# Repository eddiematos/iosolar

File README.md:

# iosolar
Design files for a modular solar power system. These files are licensed with an open-source hardware license based on the Apache License Version 2.0, known as the Solderpad Hardware Licence Version 2.

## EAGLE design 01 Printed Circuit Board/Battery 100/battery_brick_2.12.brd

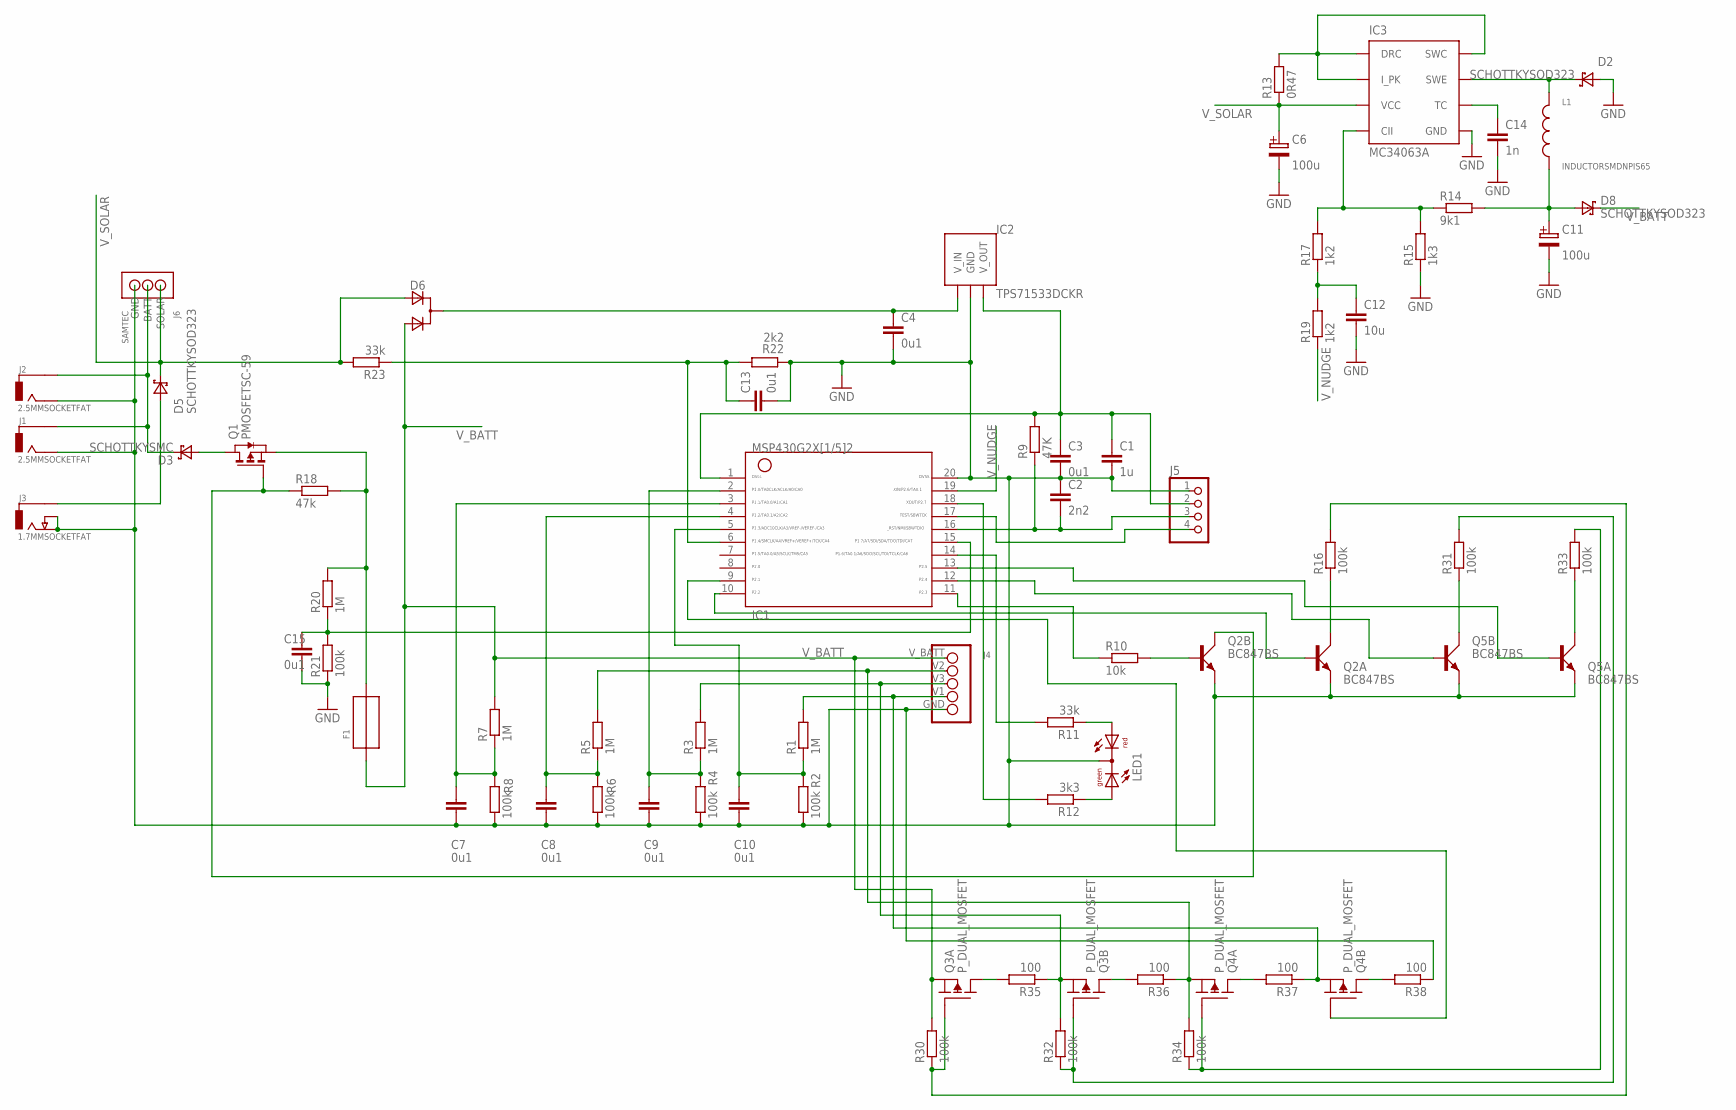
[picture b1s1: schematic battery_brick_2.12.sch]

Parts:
C1: 1u; C0603K
C2: 2n2; C0603K
C3: 0u1; C0603K
C4, C7, C8, C9, C10, C13, C15: 0u1; C0603
C6, C11: 100u; CAPCANVZH101
C12: 10u; C2012
C14: 1n; C0603
D2, D5, D8: SCHOTTKYSOD323; SOD323
D3: SCHOTTKYSMC; SMC
D6: D_2ASOT323; SOT323
F1: FUSE; 1812
IC1: G2X[1/5]2---PW20; PW20
IC2: TPS71533DCKR; SC70-5
IC3: MC34063A; SOIC8
J1, J2: 2.5MMSOCKETFAT; 2.5MMSOCKET-OBLONGFAT
J3: 1.7MMSOCKETFAT; 1.7MMSOCKET-OBLONGFAT
J4: S5B-PH-K-S
J5: PINHD-1X4; 1X04
J6: SAMTEC
L1: INDUCTORSMDNPIS65; INDUCTOR_NPIS65
LED1: DUOLED5MM
Q1: PMOSFETSC-59; SC-59
Q2, Q5: BC847BS; SOT363_PHILIPS
Q3, Q4: P_DUAL_MOSFET; SOT666
R1, R3, R5, R7: 1M; R0805
R2, R4, R6, R8: 100k; R0805
R9: 47K; R0603
R10: 10k; R0603
R11, R23: 33k; R0603
R12: 3k3; R0603
R13: 0R47; R1206
R14: 9k1; R0603
R15: 1k3; R0603
R16, R21, R30, R31, R32, R33, R34: 100k; R0603
R17, R19: 1k2; R0603
R18: 47k; R0603
R20: 1M; R0603
R22: 2k2; R0603
R35, R36, R37, R38: 100; M1206

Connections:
GND: C1.2, C2.1, C3.2, C4.2, C6.-VE, C7.2, C8.2, C9.2, C10.2, C11.-VE, C12.2, C13.2, C14.2, C15.2, D2.ANODE, IC1.20, IC2.GND, IC3.GND, J1.-VE, J2.-VE, J3.-VE, J3.P$3, J4.GND, J5.1, J6.GND, LED1.K (C), Q2.1 (E), Q2.4 (E), Q5.1 (E), Q5.4 (E), R2.1, R4.1, R6.1, R8.1, R15.1, R21.1, R22.1, R38.1
unnamed: IC1.17, J5.4
unnamed: C10.1, IC1.5, R1.1, R2.2
unnamed: F1.2, Q1.S, R18.2, R20.2
unnamed: C9.1, IC1.2, R3.1, R4.2
unnamed: D3.CATHODE, J1.+VE, J2.+VE, J6.BATT
unnamed: C8.1, IC1.4, R5.1, R6.2
unnamed: C7.1, IC1.3, R7.1, R8.2
unnamed: C15.1, IC1.15, R20.1, R21.2
unnamed: Q2.5 (B), R10.2
unnamed: IC1.14, R11.2
unnamed: J4.V1, Q4.4 (S), R1.2, R37.1
unnamed: D5.ANODE, J3.+VE
unnamed: LED1.AG, R12.1
unnamed: LED1.AR, R11.1
unnamed: J4.V3, Q3.4 (S), R3.2, R32.2, R35.1
unnamed: J4.V2, Q4.1 (S), R5.2, R34.2, R36.1
unnamed: IC3.DRC, IC3.I_PK, IC3.SWC, R13.2
unnamed: D3.ANODE, Q1.D
unnamed: Q1.G, Q2.3 (C), R18.1
unnamed: IC1.18, R12.2
unnamed: IC3.CII, R14.1, R15.2, R17.2
unnamed: D2.CATHODE, IC3.SWE, L1.P$1
unnamed: C13.1, IC1.6, R22.2, R23.1
unnamed: C12.1, R17.1, R19.2
unnamed: C11.+VE (P$1+), D8.ANODE, L1.P$2, R14.2
unnamed: C14.1, IC3.TC
unnamed: Q3.6 (D), R35.2
unnamed: Q5.3 (C), R31.1
unnamed: IC1.9, Q4.5 (G)
unnamed: C2.2, IC1.16, J5.3, R9.1
unnamed: Q3.2 (G), R16.2, R30.1
unnamed: Q3.5 (G), R31.2, R32.1
unnamed: Q4.2 (G), R33.2, R34.1
unnamed: Q5.6 (C), R33.1
unnamed: Q2.6 (C), R16.1
unnamed: Q4.3 (D), R38.2
unnamed: IC1.11, R10.1
unnamed: IC1.10, Q2.2 (B)
unnamed: IC1.12, Q5.5 (B)
unnamed: IC1.13, Q5.2 (B)
unnamed: Q3.3 (D), R36.2
unnamed: Q4.6 (D), R37.2
VCC: C1.1, C3.1, IC1.1, IC2.OUT (V_OUT), J5.2, R9.2
V_BATT: D6.3 (A2), D8.CATHODE, F1.1, J4.V_BATT, Q3.1 (S), R7.2, R30.2
V_NUDGE: IC1.19, R19.1
V_REGIN: C4.1, D6.1 (C), IC2.IN (V_IN)
V_SOLAR: C6.+VE (P$1+), D5.CATHODE, D6.2 (A1), IC3.VCC, J6.SOLAR, R13.1, R23.2

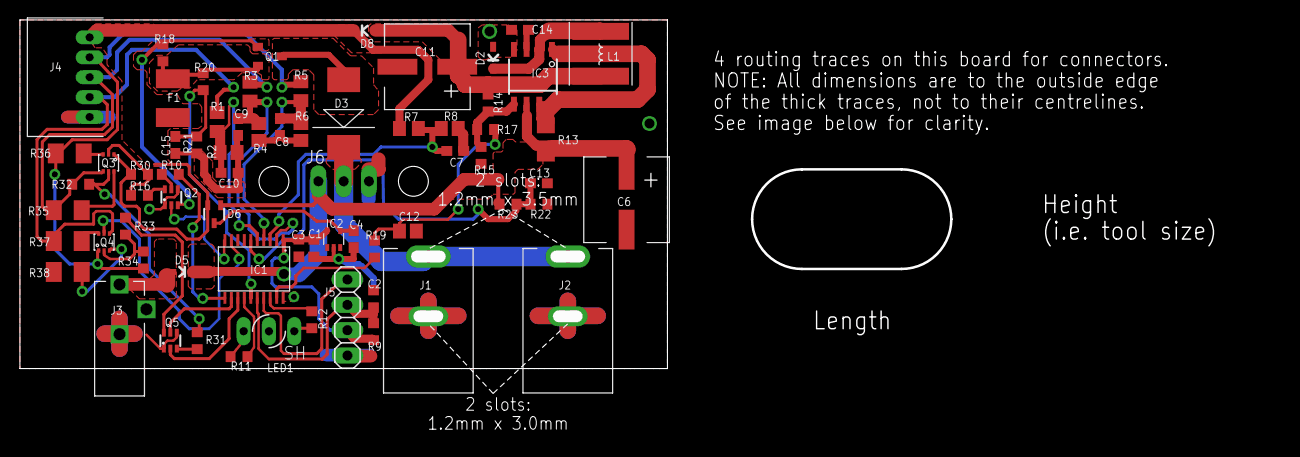
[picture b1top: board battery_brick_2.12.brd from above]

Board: 2 copper layers, 65.0 x 35.0 mm, 68 parts (0 on the bottom side), 48 nets.

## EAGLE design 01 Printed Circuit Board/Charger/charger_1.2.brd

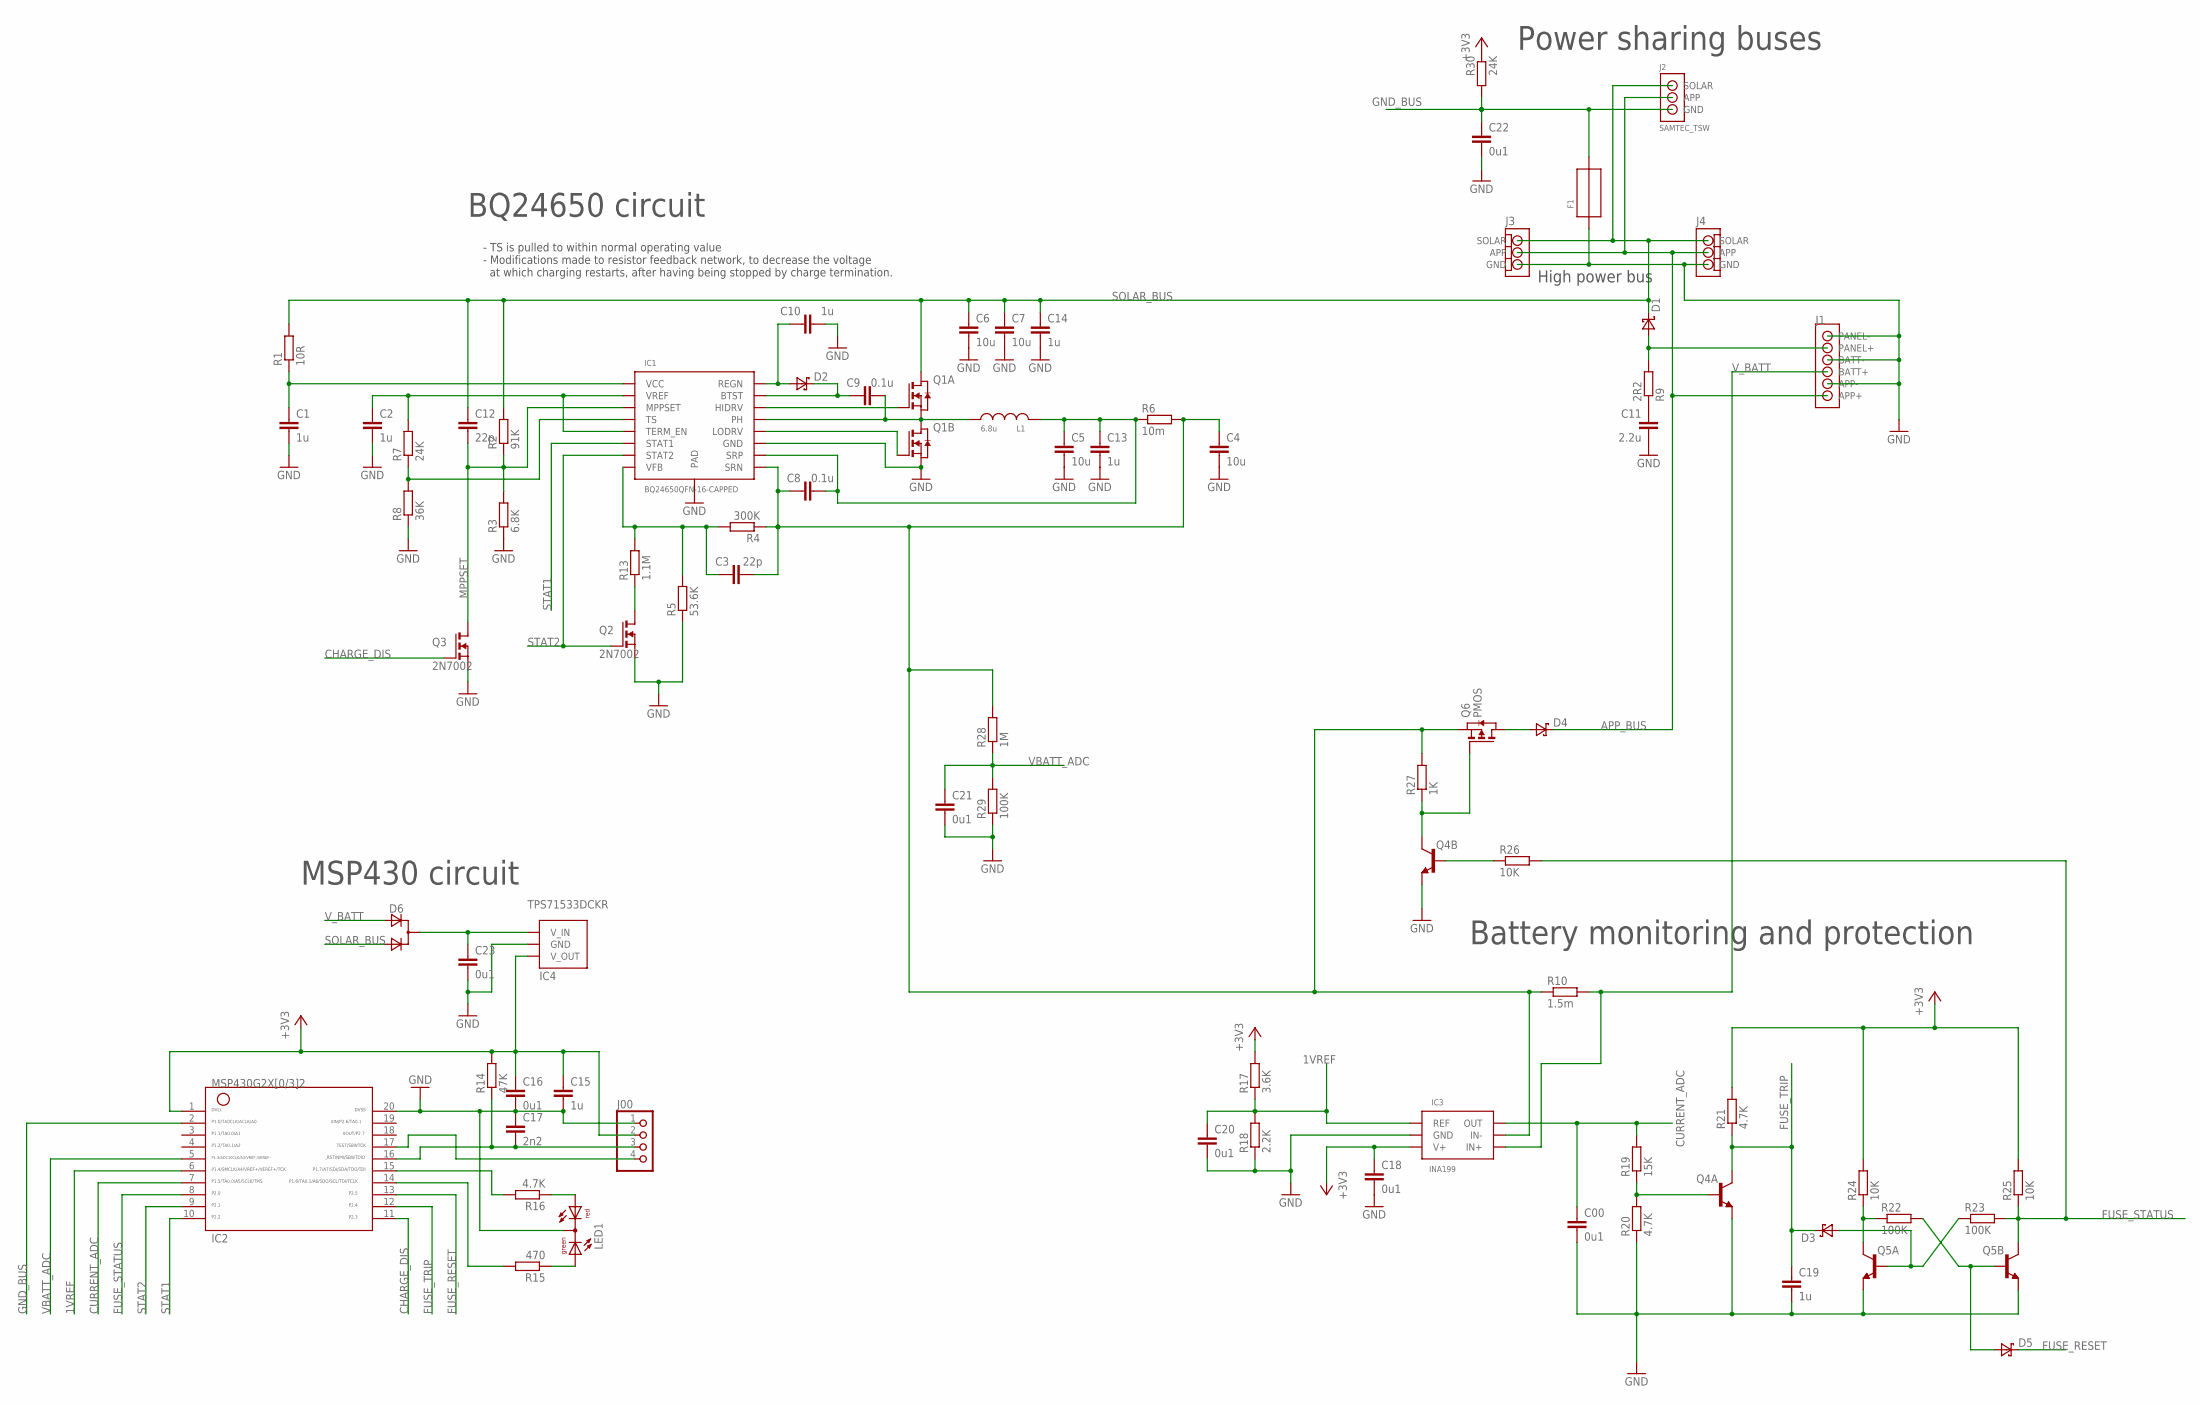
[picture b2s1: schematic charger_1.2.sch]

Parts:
C00, C16, C18, C20, C21, C22, C23: 0u1; C0603K
C1, C2, C10, C13, C14, C19: 1u; C0603
C3, C12: 22p; C0603
C4, C5, C6, C7: 10u; C1206
C8, C9: 0.1u; C0603
C11: 2.2u; C0603
C15: 1u; C0603K
C17: 2n2; C0603K
D1: SCHOTTKYDPAK; DPAK
D2: SCHOTTKYSOT23; SOT23
D3, D5: SCHOTTKYSOD-523F; SOD-523F
D4: SCHOTTKYSO8-FLAT; SO8-FLAT
D6: D_2ASOT23; SOT-23
F1: FUSE2920; 2920
IC1: BQ24650QFN-16-CAPPED; QFN-16-CAPPED
IC2: G2X[0/3]2---PW20; PW20
IC3: INA199; SC70-6
IC4: TPS71533DCKR; SC70-5
J00: PINHD-1X4; 1X04
J1: TERMINALBLOCK
J2: SAMTEC_TSW
J3: TERMINALBLOCK_3_REV
J4: TERMINALBLOCK_3
L1: 6.8u; INDUCTOR
LED1: DUOLED5MM
Q1: SI7288DP; POWERPAK-SO8-DUAL
Q2, Q3: 2N7002; SOT23
Q4, Q5: DUALNPN; SC70-6
Q6: PMOS; POWERPAK-SO8
R1: 10R; R0603
R2: 91K; R0603
R3: 6.8K; R0603
R4: 300K; R0603
R5: 53.6K; R0805
R6: 10m; R1206
R7, R30: 24K; R0603
R8: 36K; R0603
R9: 2R2; R0603
R10: 1.5m; R2010
R13: 1.1M; R0603
R14: 47K; R0603
R15: 470; R0603
R16, R20, R21: 4.7K; R0603
R17: 3.6K; R0603
R18: 2.2K; R0603
R19: 15K; R0603
R22, R23, R29: 100K; R0603
R24, R25, R26: 10K; R0603
R27: 1K; R0603
R28: 1M; R0805

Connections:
1VREF: C20.1, IC2.6, IC3.EMITTER-B-1 (REF), R17.1, R18.2
+3V3: C15.1, C16.1, C18.1, IC2.1, IC3.COLLECTOR-A-3 (V+), IC4.OUT (V_OUT), J00.2, R14.2, R17.2, R21.2, R24.2, R25.2, R30.1
APP_BUS: D4.CATHODE, J1.APP+, J2.APP, J3.APP, J4.APP
CHARGE_DIS: IC2.11, Q3.ANODE (G)
CURRENT_ADC: C00.1, IC2.7, IC3.COLLECTOR-B-6 (OUT), R19.2
FUSE_RESET: D5.CATHODE, IC2.13
FUSE_STATUS: IC2.8, Q5.COLLECTOR-B-6 (COLLECTOR), R23.2, R25.1, R26.2
FUSE_TRIP: C19.1, D3.CATHODE, IC2.12, Q4.COLLECTOR-A-3 (COLLECTOR), R21.1
GND: C00.2, C1.2, C2.2, C4.2, C5.2, C6.2, C7.2, C10.2, C11.2, C13.2, C14.2, C15.2, C16.2, C17.1, C18.2, C19.2, C20.2, C21.2, C22.2, C23.2, F1.P$1, IC1.GND-P11 (GND), IC1.P$17 (PAD), IC1.P$18 (PAD), IC1.P$19 (PAD), IC1.P$20 (PAD), IC2.20, IC3.BASE-B-2 (GND), IC4.GND, J00.1, J1.APP-, J1.BATT-, J1.PANEL-, J3.GND, J4.GND, LED1.K (C), Q1.S2 (S), Q2.NC (S), Q3.NC (S), Q4.EMITTER-B-1 (EMMITER), Q4.EMMITER-A-4 (EMMITER), Q5.EMITTER-B-1 (EMMITER), Q5.EMMITER-A-4 (EMMITER), R3.1, R5.1, R8.1, R18.1, R20.1, R29.1
GND_BUS: C22.1, F1.P$2, IC2.2, J2.GND, R30.2
MPPSET: C12.2, IC1.MPPSET-P2 (MPPSET), Q3.CATHODE (D), R2.1, R3.2
unnamed: IC2.15, R16.2
unnamed: IC1.HIDRV-P15 (HIDRV), Q1.G1 (G)
unnamed: Q2.CATHODE (D), R13.1
unnamed: LED1.AR, R16.1
unnamed: C9.2, IC1.PH-P14 (PH), L1.P$2, Q1.D2A (D), Q1.D2B (D), Q1.D2C (D), Q1.S1 (S)
unnamed: IC1.TS-P4 (TS), R7.1, R8.2
unnamed: C9.1, D2.CATHODE, IC1.BTST-P16 (BTST)
unnamed: IC1.LODRV-P13 (LODRV), Q1.G2 (G)
unnamed: C3.1, IC1.VFB-P8 (VFB), R4.2, R5.2, R13.2
unnamed: C10.1, D2.ANODE, IC1.REGN-P12 (REGN)
unnamed: IC2.17, J00.4
unnamed: Q4.BASE-A-5 (BASE), R19.1, R20.2
unnamed: LED1.AG, R15.1
unnamed: D5.ANODE, Q5.BASE-B-2 (BASE), R22.2
unnamed: Q5.COLLECTOR-A-3 (COLLECTOR), R22.1, R24.1
unnamed: C2.1, IC1.TERM_EN-P7 (TERM_EN), IC1.VREF-P6 (VREF), R7.2
unnamed: D3.ANODE, Q5.BASE-A-5 (BASE), R23.1
unnamed: Q4.COLLECTOR-B-6 (COLLECTOR), Q6.G, R27.1
unnamed: D4.ANODE1 (ANODE), D4.ANODE2 (ANODE), D4.ANODE3 (ANODE), Q6.D1 (D), Q6.D2 (D), Q6.D3 (D), Q6.D4 (D)
unnamed: IC2.14, R15.2
unnamed: Q4.BASE-B-2 (BASE), R26.1
unnamed: C23.1, D6.1 (C), IC4.IN (V_IN)
unnamed: C17.2, IC2.16, J00.3, R14.1
SOLAR_BUS: C6.1, C7.1, C12.1, C14.1, D1.CATHODE, D6.3 (A2), J2.SOLAR, J3.SOLAR, J4.SOLAR, Q1.D1A (D), Q1.D1B (D), Q1.D1C (D), R1.2, R2.2
SOLAR_IN: D1.ANODE1 (ANODE), D1.ANODE2 (ANODE), J1.PANEL+, R9.2
SRP: C5.1, C8.2, C13.1, IC1.SRP-P10 (SRP), L1.P$1, R6.1
STAT1: IC1.STAT1-P3 (STAT1), IC2.10
STAT2: IC1.STAT2-P5 (STAT2), IC2.9, Q2.ANODE (G)
VBATT_ADC: C21.1, IC2.5, R28.1, R29.2
VCC: C1.1, IC1.VCC-P1 (VCC), R1.1
VCC1: C11.1, R9.1
V_BATT: D6.2 (A1), IC3.EMMITER-A-4 (IN+), J1.BATT+, R10.2
V_CHARGE: C3.2, C4.1, C8.1, IC1.SRN-P9 (SRN), IC3.BASE-A-5 (IN-), Q6.S1 (S), Q6.S2 (S), Q6.S3 (S), R4.1, R6.2, R10.1, R27.2, R28.2

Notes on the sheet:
BQ24650 circuit
- TS is pulled to within normal operating value - Modifications made to resistor feedback network, to decrease the voltage at which charging restarts, after having being stopped by charge termination.
MSP430 circuit
High power bus
Power sharing buses
Battery monitoring and protection

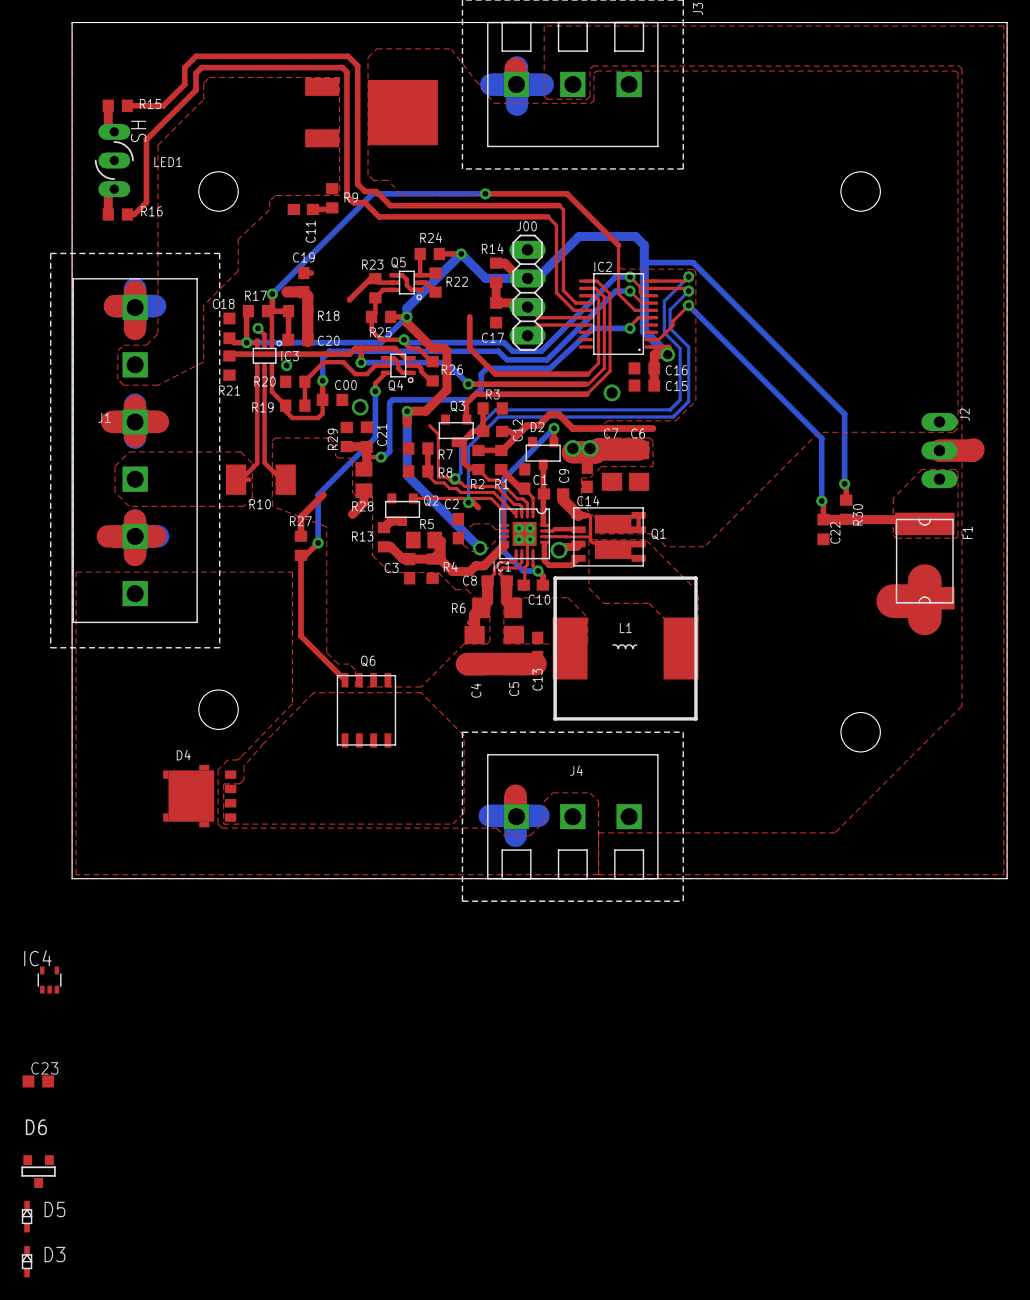
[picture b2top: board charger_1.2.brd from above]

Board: 2 copper layers, 83.0 x 76.0 mm, 76 parts (0 on the bottom side), 44 nets.

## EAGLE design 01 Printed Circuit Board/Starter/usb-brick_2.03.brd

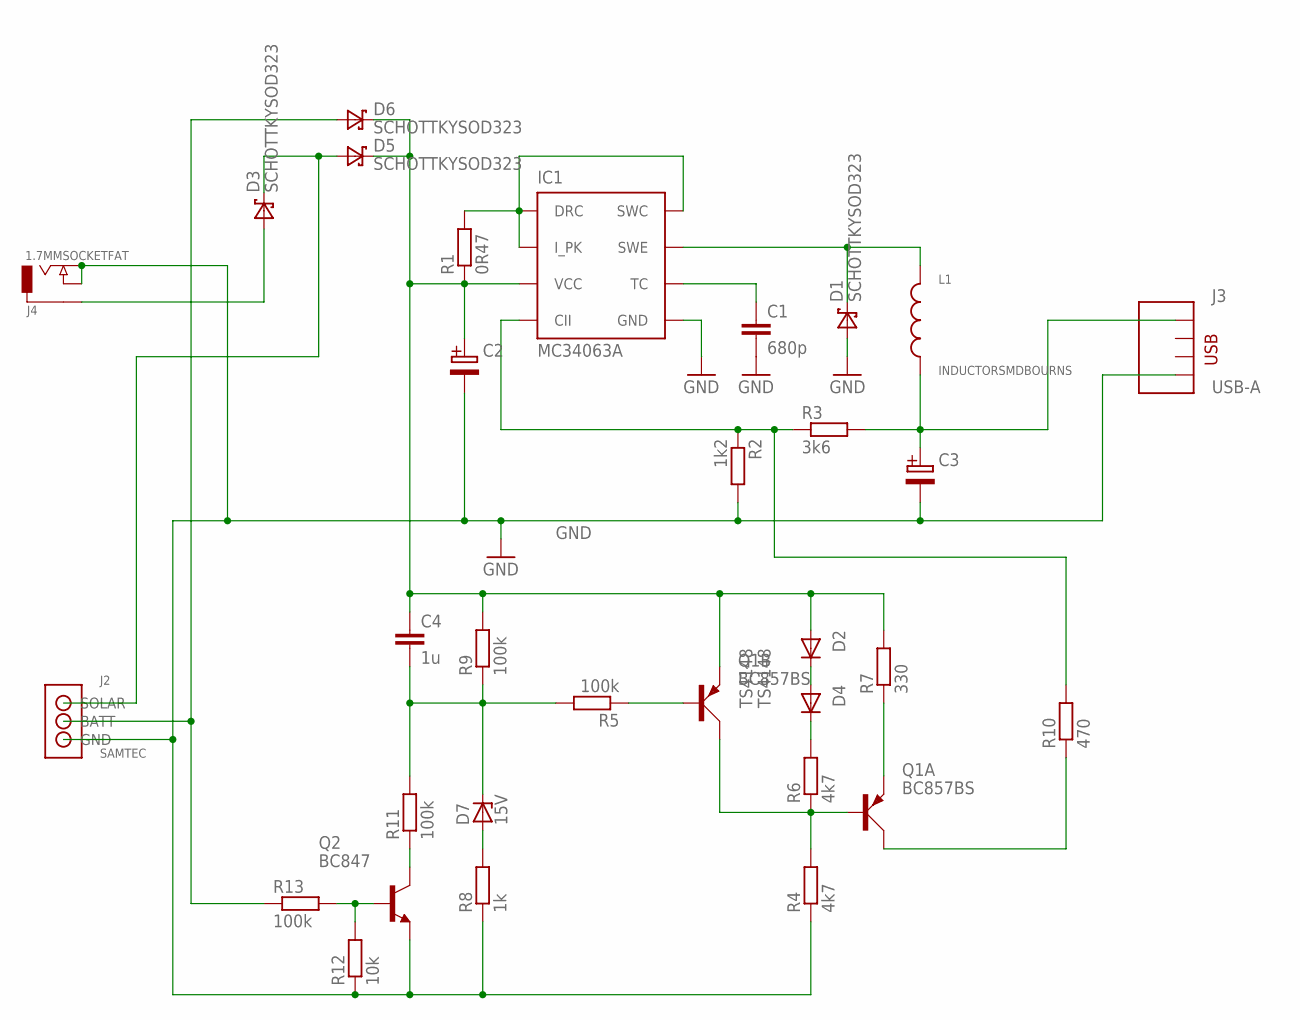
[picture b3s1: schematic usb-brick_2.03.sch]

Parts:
C1: 680p; C0603
C2, C3: ELEC_CAP_CANVZH101; CAPCANVZH101
C4: 1u; C0603
D1, D3, D5, D6: SCHOTTKYSOD323; SOD323
D2, D4: TS4148; 0805
D7: 15V; SOT23
IC1: MC34063A; SOIC8
J2: SAMTEC
J3: USB-A
J4: 1.7MMSOCKETFAT; 1.7MMSOCKET-OBLONGFAT
L1: INDUCTORSMDBOURNS; INDUCTOR_BOURNS
Q1: BC857BS; SOT363_PHILIPS
Q2: BC847; SOT23
R1: 0R47; R1206
R2: 1k2; R0603
R3: 3k6; R0603
R4, R6: 4k7; R0603
R5, R9, R11, R13: 100k; R0603
R7: 330; R0603
R8: 1k; R0603
R10: 470; R0603
R12: 10k; R0603

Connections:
C3: C3.+VE (P$1+), J3.5V, L1.P$2, R3.2
GND: C1.2, C2.-VE, C3.-VE, D1.ANODE, IC1.GND, J2.GND, J3.GND, J4.-VE, J4.P$3, Q2.2 (E), R2.2, R4.1, R8.1, R12.1
unnamed: D1.CATHODE, IC1.SWE, L1.P$1
unnamed: D3.CATHODE, D5.ANODE, J2.SOLAR
unnamed: C2.+VE (P$1+), C4.1, D2.A, D5.CATHODE, D6.CATHODE, IC1.VCC, Q1.4 (E), R1.1, R7.2, R9.2
unnamed: IC1.CII, R2.1, R3.1, R10.2
unnamed: C1.1, IC1.TC
unnamed: Q1.2 (B), Q1.3 (C), R4.2, R6.1
unnamed: Q1.6 (C), R10.1
unnamed: D3.ANODE, J4.+VE
unnamed: C4.2, D7.3 (C), R5.2, R9.1, R11.2
unnamed: D2.C, D4.A
unnamed: Q1.1 (E), R7.1
unnamed: IC1.DRC, IC1.I_PK, IC1.SWC, R1.2
unnamed: Q1.5 (B), R5.1
unnamed: D7.1 (A), R8.2
unnamed: D4.C, R6.2
unnamed: Q2.1 (B), R12.2, R13.2
unnamed: Q2.3 (C), R11.1
unnamed: D6.ANODE, J2.BATT, R13.1

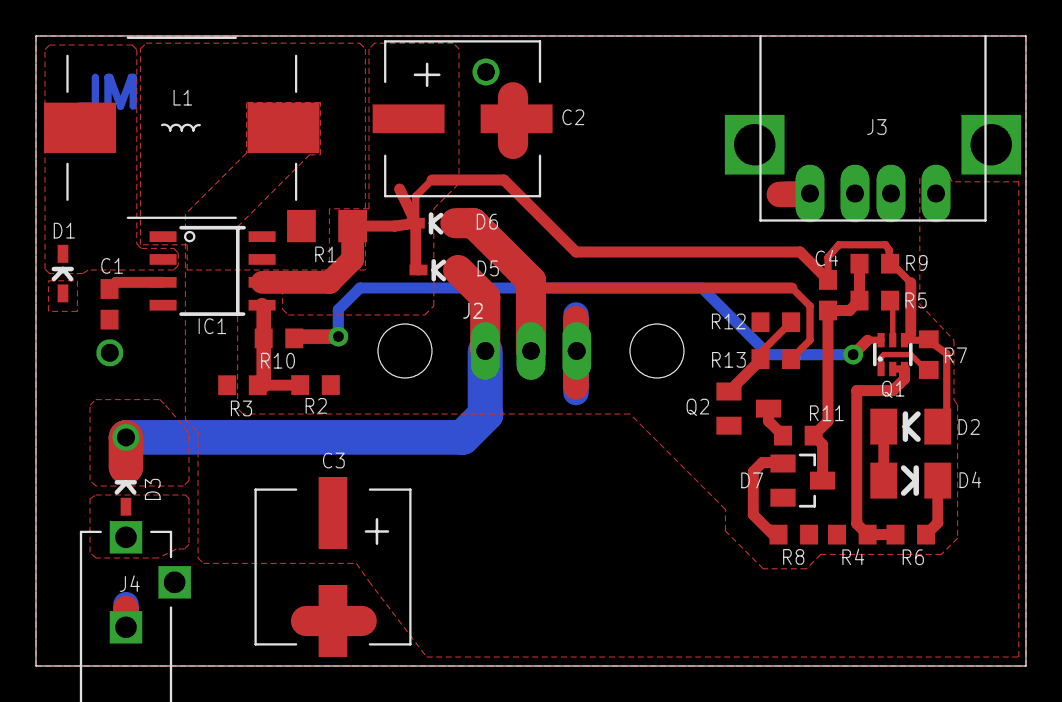
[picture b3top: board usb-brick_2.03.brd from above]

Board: 2 copper layers, 55.0 x 35.0 mm, 31 parts (0 on the bottom side), 20 nets.
